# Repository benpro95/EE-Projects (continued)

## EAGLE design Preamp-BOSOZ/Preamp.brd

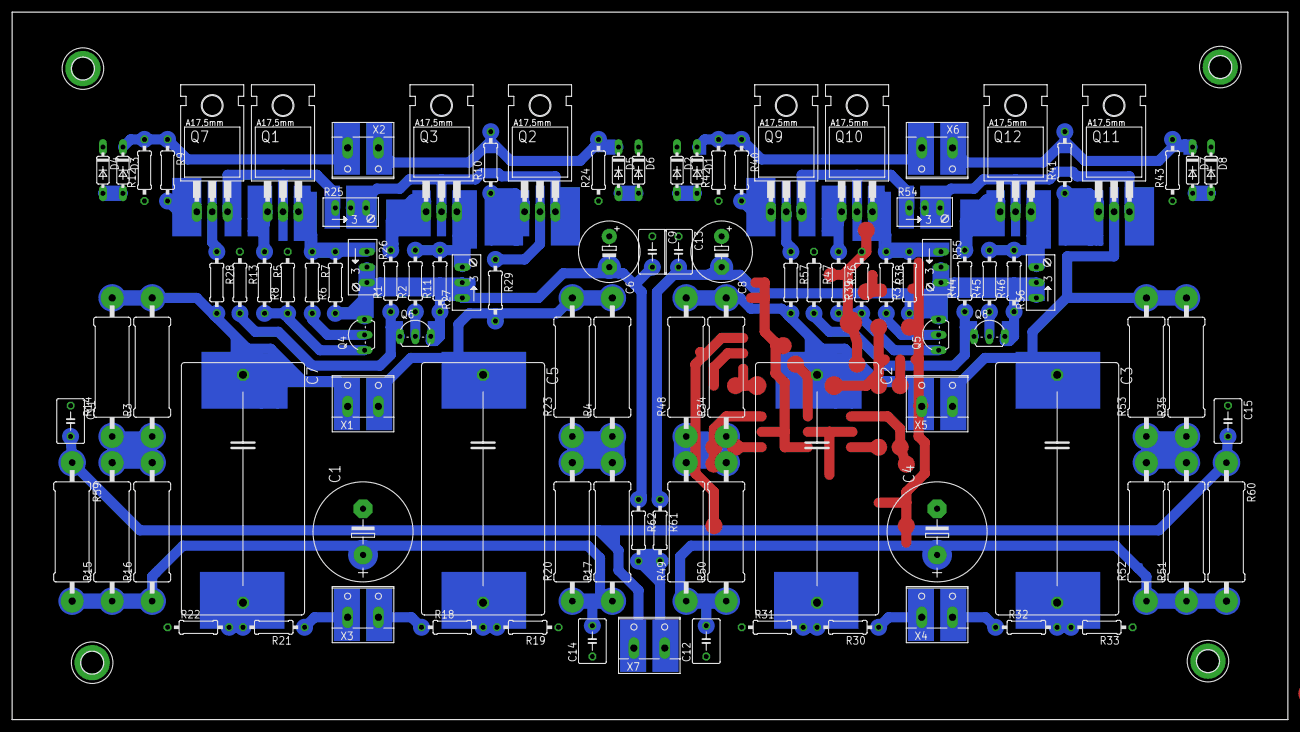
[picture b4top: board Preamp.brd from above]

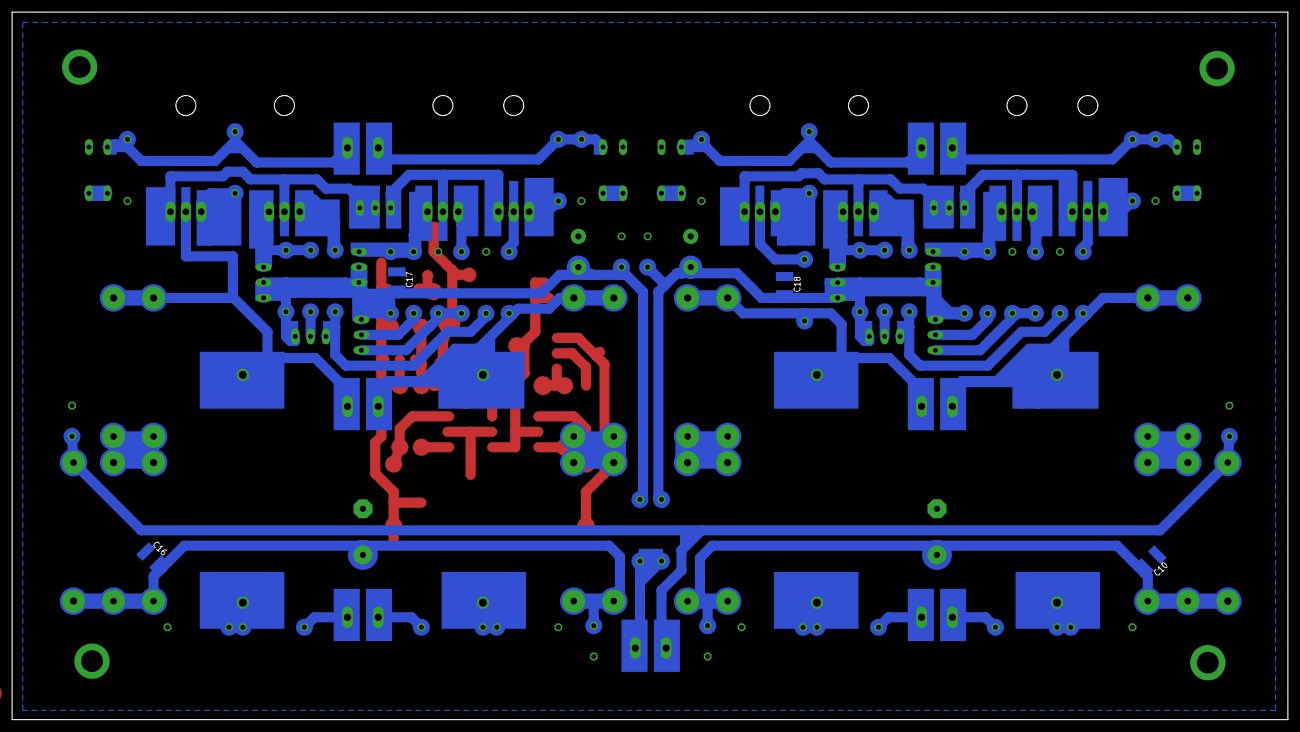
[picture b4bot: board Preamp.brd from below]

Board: 2 copper layers, 210.5 x 116.8 mm, 110 parts (4 on the bottom side), 58 nets.

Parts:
C1, C4: 220uF; E7,5-16
C2, C3, C5, C7: 11uF; C375-203X418
C6, C8: 100uF; E5-10,5
C9, C11, C12, C13, C14, C15: .6; C050-045X075
C10, C16, C17, C18: 3n9; C1210K
D1, D2, D3, D4, D5, D6, D7, D8: 9V1; DO35-7
H1, H2, H3, H4: MOUNT-PAD-ROUND3.6; 3,6-PAD
Q1, Q2, Q3, Q7, Q9, Q10, Q11, Q12: NFET; TO220BH
Q4, Q5, Q6, Q8: BC546A; TO92-EBC
R1, R2, R5, R7, R9, R10, R18, R21, R30, R32, R36, R38, R40, R41, R44, R45: 200; 0207/10
R3, R4, R14, R15, R16, R17, R20, R23, R34, R35, R48, R49, R50, R51, R52, R53: 1K; 0617/22
R6, R11, R37, R46: 27; 0207/10
R8, R13, R39, R47: 1K8; 0207/10
R12, R24, R42, R43: 24K5; 0207/10
R19, R22, R31, R33: 200K; 0207/10
R25, R54: 1K; RJ9W
R26, R27, R55, R56: 500; RJ9W
R28, R29, R57: 0; 0207/10
R59, R60: 47; 0617/22
R61, R62: 5R1; 0207/10
X1, X2, X3, X4, X5, X6, X7: W237-132

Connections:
GND: C1.-, C4.-, C6.+, C8.+, C9.1, C10.1, C11.1, C12.1, C13.1, C14.1, C15.1, C16.1, C17.1, C18.1, D2.C, D4.C, D6.C, D8.C, R8.2, R12.1, R13.1, R19.1, R22.1, R24.1, R31.1, R33.1, R39.2, R42.1, R43.1, R47.1
unnamed: Q3.S, R2.2, R11.2, R27.A
unnamed: Q3.G, R1.2
unnamed: Q6.B, R2.1
unnamed: Q6.C, R1.1, R13.2
unnamed: Q1.G, R5.1
unnamed: C6.-, C9.2, C18.2, Q4.E, Q6.E, R6.1, R11.1, R26.A, R26.S, R27.E, R27.S, R62.1
unnamed: Q4.B, R7.2
unnamed: Q1.S, R6.2, R7.1, R26.E
unnamed: Q4.C, R5.2, R8.1
unnamed: Q7.G, R9.2
unnamed: R3.1, R14.1, R15.2, R16.2
unnamed: Q2.G, R10.1
unnamed: C7.1, R3.2, R14.2, R28.2, X1.1
unnamed: Q1.D, Q7.S, R25.E
unnamed: D3.C, R9.1, R12.2, X2.2
unnamed: Q2.S, Q3.D, R25.A, R25.S
unnamed: D5.C, R10.2, R24.2, X2.1
unnamed: Q7.D, R28.1
unnamed: R4.1, R17.2, R20.2, R23.1
unnamed: Q2.D, R29.1
unnamed: R21.1, X3.1
unnamed: C1.+, C10.2, C14.2, R15.1, R16.1, R17.1, R20.1, R59.2
unnamed: C2.1, R34.2, R48.2, R57.2, X5.1
unnamed: C2.2, R30.2, R31.2
unnamed: C3.2, R32.2, R33.2
unnamed: C7.2, R21.2, R22.2
unnamed: C5.2, R18.2, R19.2
unnamed: R30.1, X4.1
unnamed: C5.1, R4.2, R23.2, R29.2, X1.2
unnamed: R32.1, X4.2
unnamed: Q10.G, R36.1
unnamed: C8.-, C13.2, C17.2, Q5.E, Q8.E, R37.1, R46.1, R55.A, R55.S, R56.E, R56.S, R61.1
unnamed: Q5.B, R38.2
unnamed: Q10.S, R37.2, R38.1, R55.E
unnamed: Q5.C, R36.2, R39.1
unnamed: R18.1, X3.2
unnamed: D1.C, R40.1, R42.2, X6.2
unnamed: D7.C, R41.2, R43.2, X6.1
unnamed: D1.A, D2.A
unnamed: D7.A, D8.A
unnamed: Q12.S, R45.2, R46.2, R56.A
unnamed: Q12.G, R44.2
unnamed: Q8.B, R45.1
unnamed: Q8.C, R44.1, R47.2
unnamed: Q9.S, Q10.D, R54.E
unnamed: Q11.S, Q12.D, R54.A, R54.S
unnamed: R34.1, R48.1, R49.2, R50.2
unnamed: R35.1, R51.2, R52.2, R53.1
unnamed: C4.+, C12.2, C16.2, R49.1, R50.1, R51.1, R52.1, R60.2
unnamed: Q9.G, R40.2
unnamed: Q11.G, R41.1
unnamed: Q9.D, R57.1
unnamed: C3.1, Q11.D, R35.2, R53.2, X5.2
unnamed: C11.2, C15.2, R59.1, R60.1, X7.1
unnamed: R61.2, R62.2, X7.2
unnamed: D3.A, D4.A
unnamed: D5.A, D6.A

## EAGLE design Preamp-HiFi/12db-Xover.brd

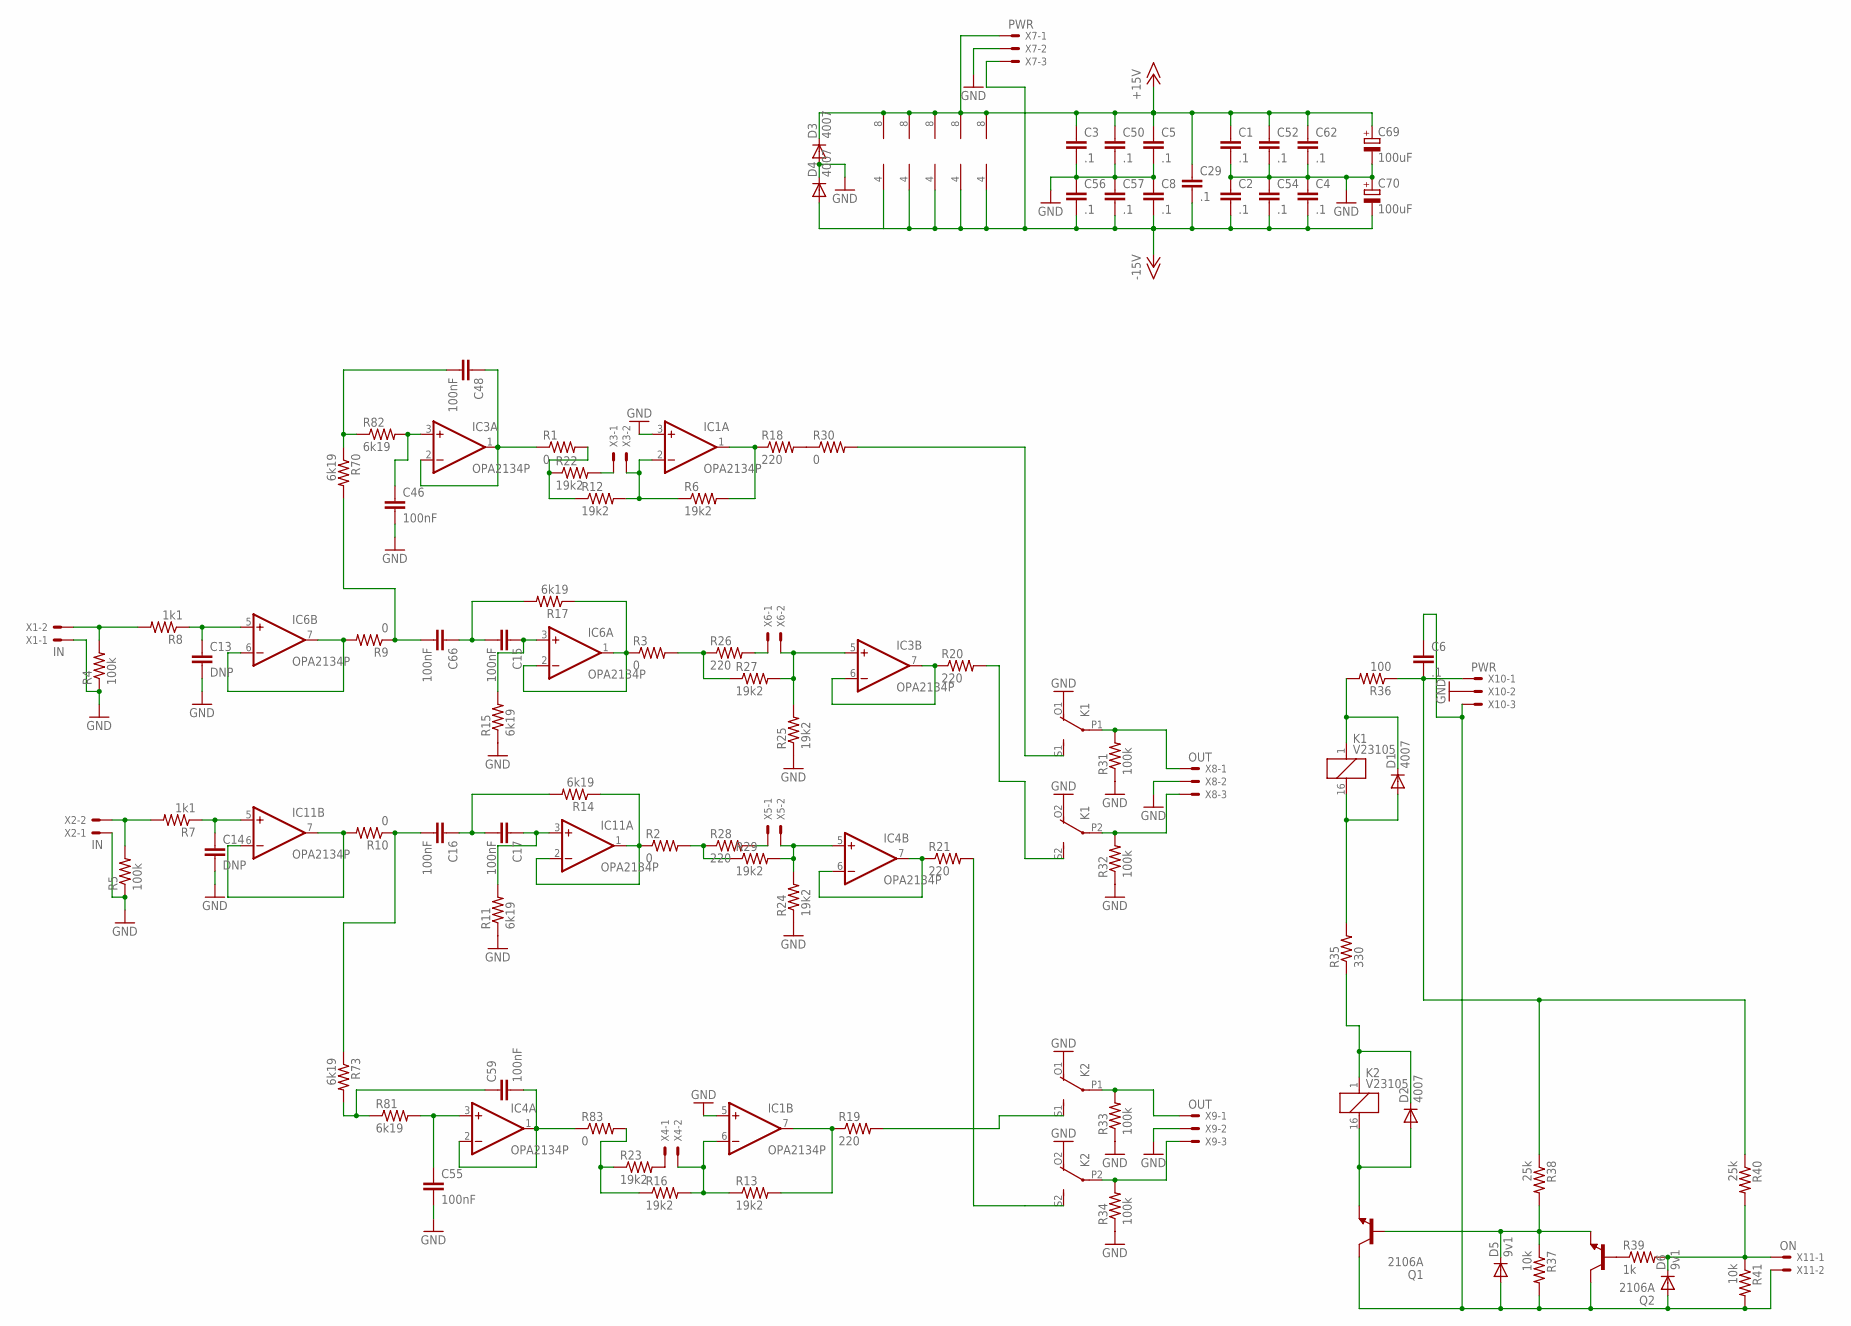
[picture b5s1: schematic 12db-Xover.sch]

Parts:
C1, C2, C3, C4, C5, C6, C8, C29, C50, C52, C54, C56, C57, C62: .1; C4532
C13, C14: DNP; C050-035X075
C15, C16, C17, C46, C48, C55, C59, C66: 100nF; C050-075X075
C69, C70: 100uF; E3,5-10
D1, D2, D3, D4: 4007; DO35-10
D5, D6: 9v1; DO35-7
IC1, IC3, IC4, IC6, IC11: OPA2134P; DIL08
K1, K2: V23105; 351
Q1, Q2: 2106A; TO92-EBC
R1, R3: 0; 0309/12
R2, R9, R10, R30, R83: 0; 0309/10
R4, R5, R31, R32, R33, R34: 100k; 0309/10
R6, R12, R13, R16, R22, R23, R27, R29: 19k2; 0309/10
R7, R8: 1k1; 0309/10
R11, R15, R70, R73, R81, R82: 6k19; 0309/12
R14, R17: 6k19; 0309/10
R18, R20: 220; 0309/12
R19, R21, R26, R28: 220; 0309/10
R24, R25: 19k2; 0309/12
R35: 330; 0411/15
R36: 100; 0309/12
R37, R41: 10k; 0309/12
R38, R40: 25k; 0309/10
R39: 1k; 0309/10
X1, X2: IN; 22-23-2021
X3, X4, X5, X6: 22-23-2021
X7, X10: PWR; 22-23-2031
X8, X9: OUT; 22-23-2031
X11: ON; 22-23-2021

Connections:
+15V: C1.1, C3.1, C5.1, C29.1, C50.1, C52.1, C62.1, C69.+, D3.C, IC1.8 (V+), IC3.8 (V+), IC4.8 (V+), IC6.8 (V+), IC11.8 (V+), X7.1
-15V: C2.2, C4.2, C8.2, C29.2, C54.2, C56.2, C57.2, C70.-, D4.A, IC1.4 (V-), IC3.4 (V-), IC4.4 (V-), IC6.4 (V-), IC11.4 (V-), X7.3
GND: C1.2, C2.1, C3.2, C4.1, C5.2, C8.1, C13.2, C14.2, C46.2, C50.2, C52.2, C54.1, C55.2, C56.1, C57.1, C62.2, C69.-, C70.+, D3.A, D4.C, IC1.3 (+IN), IC1.5 (+IN), K1.O1 (O), K1.O2 (O), K2.O1 (O), K2.O2 (O), R4.1, R5.1, R11.1, R15.1, R24.1, R25.1, R31.1, R32.1, R33.1, R34.1, X1.1, X2.1, X7.2, X8.2, X9.2, X10.2
unnamed: IC6.1 (OUT), IC6.2 (-IN), R3.1, R17.1
unnamed: IC3.5 (+IN), R25.2, R27.2, X6.2
unnamed: IC11.6 (-IN), IC11.7 (OUT), R10.2
unnamed: IC4.5 (+IN), R24.2, R29.2, X5.2
unnamed: C14.1, IC11.5 (+IN), R7.1
unnamed: R5.2, R7.2, X2.2
unnamed: R4.2, R8.2, X1.2
unnamed: C13.1, IC6.5 (+IN), R8.1
unnamed: IC6.6 (-IN), IC6.7 (OUT), R9.2
unnamed: IC1.2 (-IN), R6.1, R12.2, X3.2
unnamed: IC1.6 (-IN), R13.1, R16.2, X4.2
unnamed: C15.1, IC6.3 (+IN), R15.2
unnamed: C15.2, C66.1, R17.2
unnamed: IC1.1 (OUT), R6.2, R18.1
unnamed: C16.1, C17.2, R14.2
unnamed: C17.1, IC11.3 (+IN), R11.2
unnamed: IC3.6 (-IN), IC3.7 (OUT), R20.1
unnamed: IC4.6 (-IN), IC4.7 (OUT), R21.1
unnamed: IC1.7 (OUT), R13.2, R19.1
unnamed: R22.2, X3.1
unnamed: R1.2, R12.1, R22.1
unnamed: R16.1, R23.1, R83.2
unnamed: R23.2, X4.1
unnamed: R26.2, X6.1
unnamed: R28.2, X5.1
unnamed: R3.2, R26.1, R27.1
unnamed: R2.2, R28.1, R29.1
unnamed: IC11.1 (OUT), IC11.2 (-IN), R2.1, R14.1
unnamed: R18.2, R30.1
unnamed: K2.P2, R34.2, X9.3
unnamed: K2.P1, R33.2, X9.1
unnamed: K1.P2, R32.2, X8.3
unnamed: K1.P1, R31.2, X8.1
unnamed: K1.S1 (S), R30.2
unnamed: K1.S2 (S), R20.2
unnamed: K2.S1 (S), R19.2
unnamed: K2.S2 (S), R21.2
unnamed: D2.C, K2.1, R35.1
unnamed: D1.A, K1.16 (2), R35.2
unnamed: D1.C, K1.1, R36.2
unnamed: D2.A, K2.16 (2), Q1.E
unnamed: C6.2, R36.1, R38.1, R40.1, X10.1
unnamed: C6.1, D5.A, D6.A, Q1.C, Q2.C, R37.2, R41.2, X10.3, X11.2
unnamed: D5.C, Q1.B, Q2.E, R37.1, R38.2
unnamed: Q2.B, R39.1
unnamed: D6.C, R39.2, R40.2, R41.1, X11.1
unnamed: C66.2, R9.1, R70.2
unnamed: C59.2, IC4.1 (OUT), IC4.2 (-IN), R83.1
unnamed: C48.1, IC3.1 (OUT), IC3.2 (-IN), R1.1
unnamed: C46.1, IC3.3 (+IN), R82.2
unnamed: C48.2, R70.1, R82.1
unnamed: C59.1, R73.2, R81.1
unnamed: C55.1, IC4.3 (+IN), R81.2
unnamed: C16.2, R10.1, R73.1

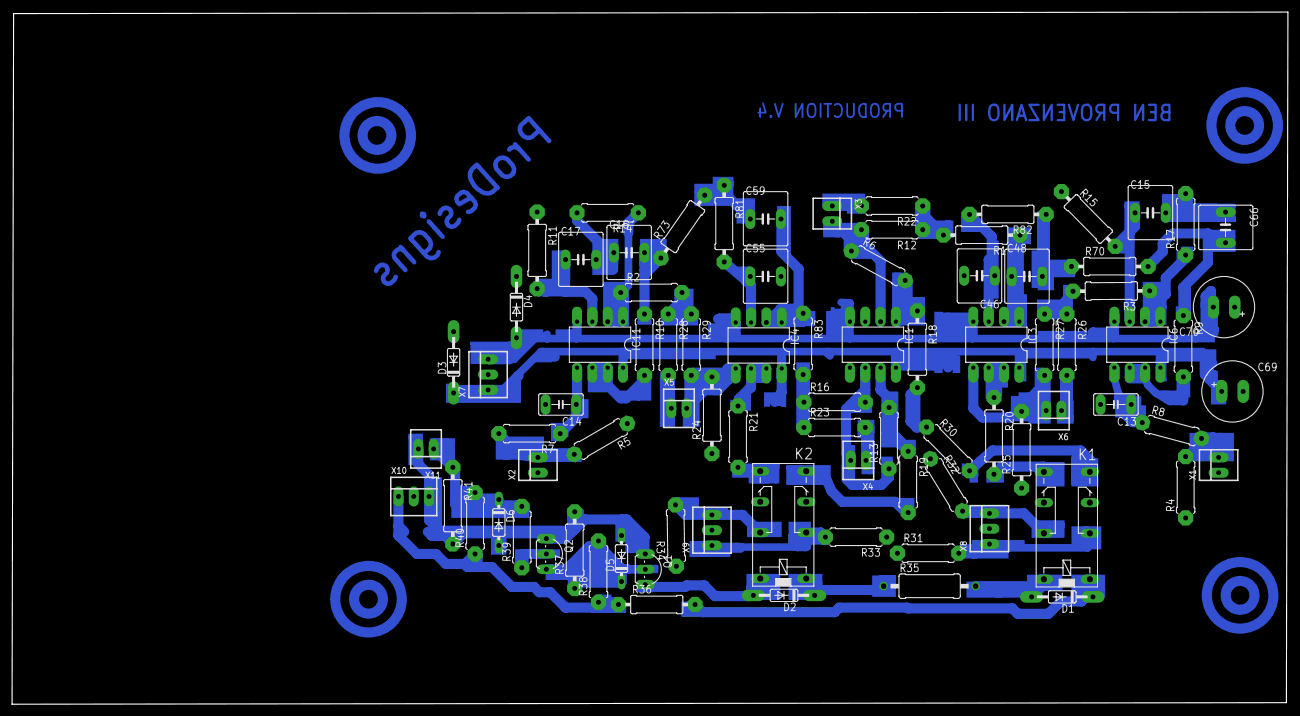
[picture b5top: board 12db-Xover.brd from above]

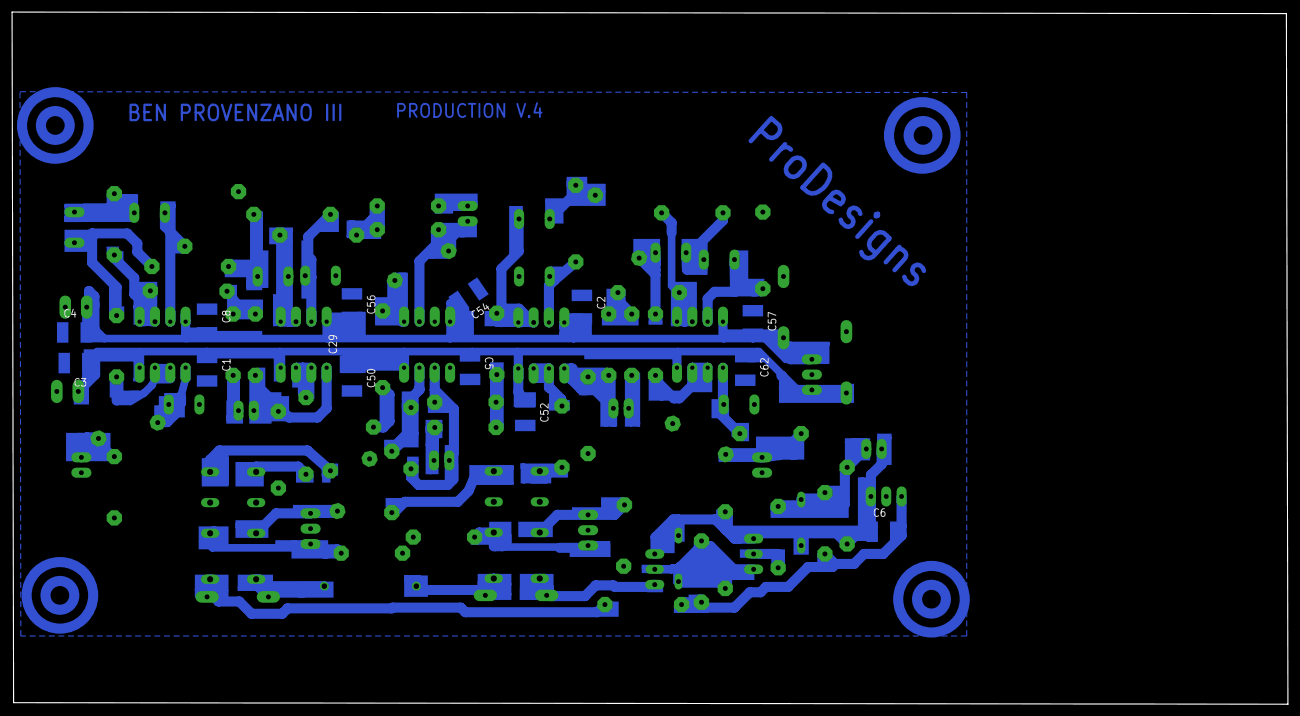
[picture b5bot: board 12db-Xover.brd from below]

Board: 2 copper layers, 211.4 x 114.7 mm, 98 parts (14 on the bottom side), 57 nets.

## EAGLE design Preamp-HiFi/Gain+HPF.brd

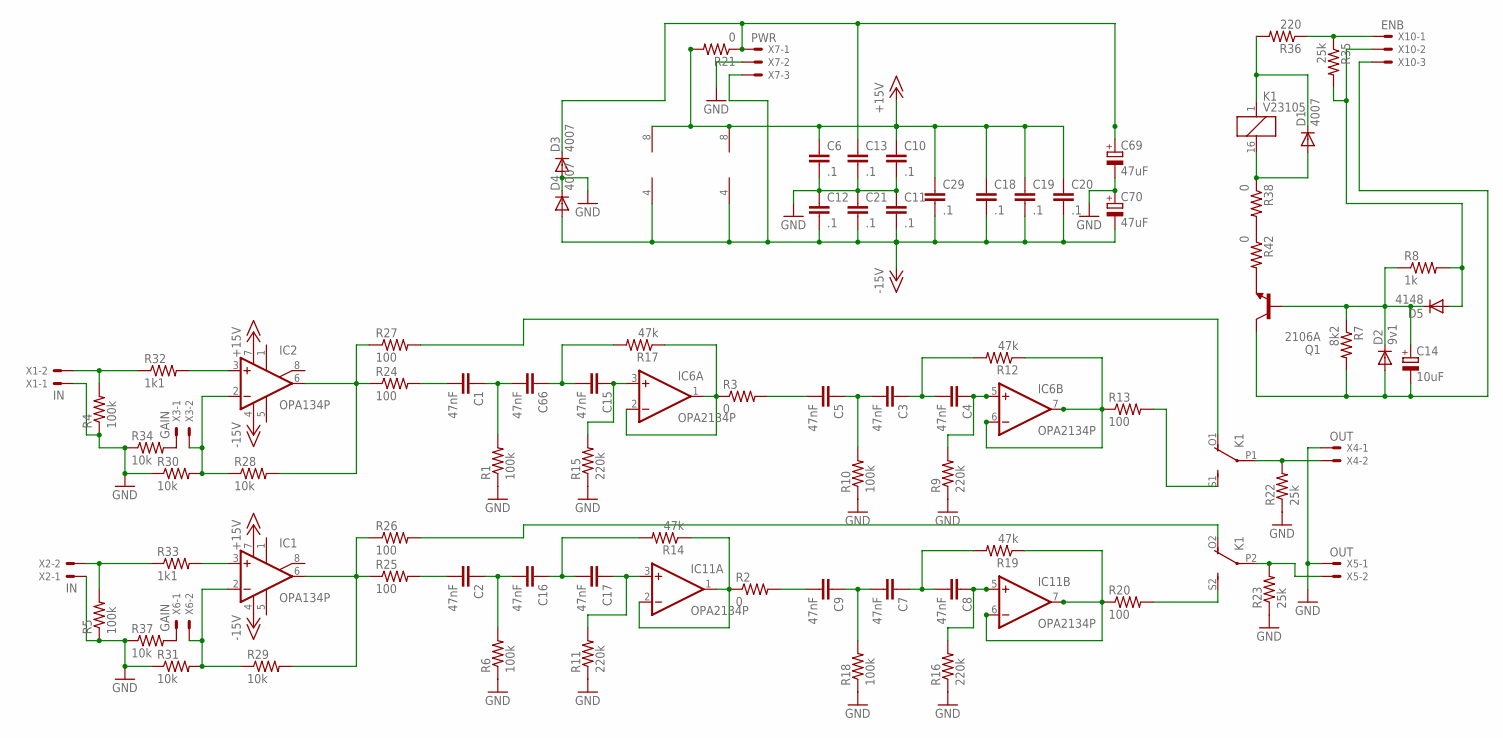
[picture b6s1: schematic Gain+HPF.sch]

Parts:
C1, C2, C3, C4, C5, C7, C8, C9, C15, C16, C17, C66: 47nF; C050-075X075
C6, C10, C11, C12, C13, C18, C19, C20, C21, C29: .1; C4532
C14: 10uF; E2,5-6
C69, C70: 47uF; E2,5-7
D1: 4007; DO35-7
D2: 9v1; DO35-7
D3, D4: 4007; DO35-10
D5: 4148; DO35-7
IC1, IC2: OPA134P; DIL08
IC6, IC11: OPA2134P; DIL08
K1: V23105; 351
Q1: 2106A; TO92-EBC
R1, R6, R10, R18: 100k; 0309/10
R2, R21, R38, R42: 0; 0309/10
R3: 0; 0309/12
R4, R5: 100k; 0309/12
R7: 8k2; R1210
R8: 1k; R1210
R9, R11, R15, R16: 220k; 0309/10
R12, R14, R17, R19: 47k; 0309/10
R13, R20, R26, R27: 100; 0309/10
R22, R23, R35: 25k; 0309/10
R24, R25: 100; 0309/12
R28, R29, R30, R31, R34, R37: 10k; 0309/10
R32, R33: 1k1; 0309/10
R36: 220; 0309/10
X1, X2: IN; 22-23-2021
X3, X6: GAIN; 22-23-2021
X4, X5: OUT; 22-23-2021
X7: PWR; 22-23-2031
X10: ENB; 22-23-2031

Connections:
+15V: C6.1, C10.1, C18.1, C19.1, C20.1, C29.1, IC1.7 (V+), IC2.7 (V+), IC6.8 (V+), IC11.8 (V+), R21.2
-15V: C11.2, C12.2, C18.2, C19.2, C20.2, C21.2, C29.2, C70.-, D4.A, IC1.4 (V-), IC2.4 (V-), IC6.4 (V-), IC11.4 (V-), X7.3
GND: C6.2, C10.2, C11.1, C12.1, C13.2, C21.1, C69.-, C70.+, D3.A, D4.C, R1.1, R4.1, R5.1, R6.1, R9.1, R10.1, R11.1, R15.1, R16.1, R18.1, R22.1, R23.1, R30.1, R31.1, R34.1, R37.1, X1.1, X2.1, X4.1, X5.1, X7.2
unnamed: IC6.1 (OUT), IC6.2 (-IN), R3.1, R17.1
unnamed: IC6.6 (-IN), IC6.7 (OUT), R12.1, R13.1
unnamed: C4.1, IC6.5 (+IN), R9.2
unnamed: C3.1, C4.2, R12.2
unnamed: R5.2, R33.1, X2.2
unnamed: R4.2, R32.1, X1.2
unnamed: C14.-, D2.A, Q1.C, R7.2, X10.3
unnamed: C3.2, C5.1, R10.2
unnamed: C5.2, R3.2
unnamed: IC11.6 (-IN), IC11.7 (OUT), R19.1, R20.1
unnamed: C15.1, IC6.3 (+IN), R15.2
unnamed: C15.2, C66.1, R17.2
unnamed: C8.1, IC11.5 (+IN), R16.2
unnamed: C16.1, C17.2, R14.2
unnamed: C17.1, IC11.3 (+IN), R11.2
unnamed: C7.1, C8.2, R19.2
unnamed: C7.2, C9.1, R18.2
unnamed: IC2.6 (OUT), R24.1, R27.1, R28.2
unnamed: IC1.6 (OUT), R25.1, R26.1, R29.2
unnamed: K1.S1 (S), R13.2
unnamed: K1.S2 (S), R20.2
unnamed: C13.1, C69.+, D3.C, R21.1, X7.1
unnamed: K1.O1 (O), R27.2
unnamed: K1.O2 (O), R26.2
unnamed: C1.2, R24.2
unnamed: C9.2, R2.2
unnamed: IC11.1 (OUT), IC11.2 (-IN), R2.1, R14.1
unnamed: C2.2, R25.2
unnamed: IC2.3 (+IN), R32.2
unnamed: IC2.2 (-IN), R28.1, R30.2, X3.2
unnamed: K1.P2, R23.2, X5.2
unnamed: K1.P1, R22.2, X4.2
unnamed: IC1.3 (+IN), R33.2
unnamed: IC1.2 (-IN), R29.1, R31.2, X6.2
unnamed: R34.2, X3.1
unnamed: R37.2, X6.1
unnamed: C14.+, D2.C, D5.C, Q1.B, R7.1, R8.1
unnamed: D1.A, K1.16 (2), R38.1
unnamed: D1.C, K1.1, R36.2
unnamed: R35.1, R36.1, X10.1
unnamed: D5.A, R8.2, R35.2, X10.2
unnamed: Q1.E, R42.2
unnamed: R38.2, R42.1
unnamed: C1.1, C66.2, R1.2
unnamed: C2.1, C16.2, R6.2

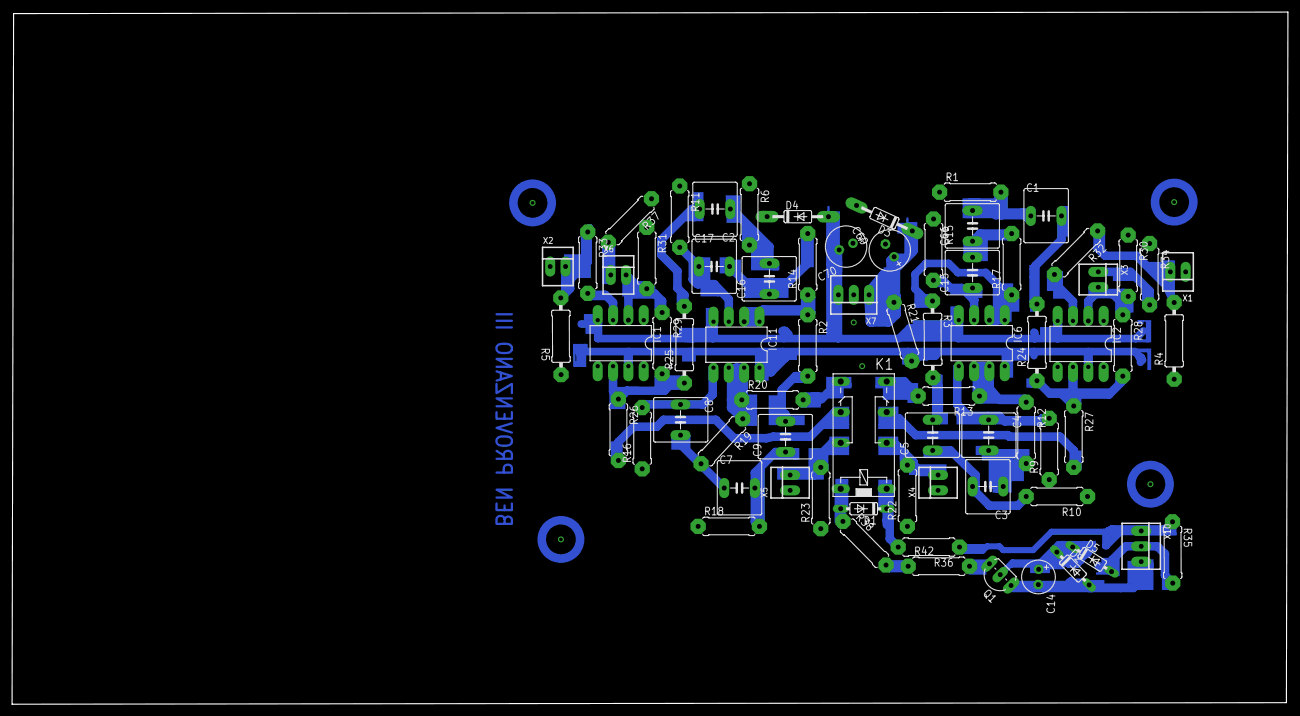
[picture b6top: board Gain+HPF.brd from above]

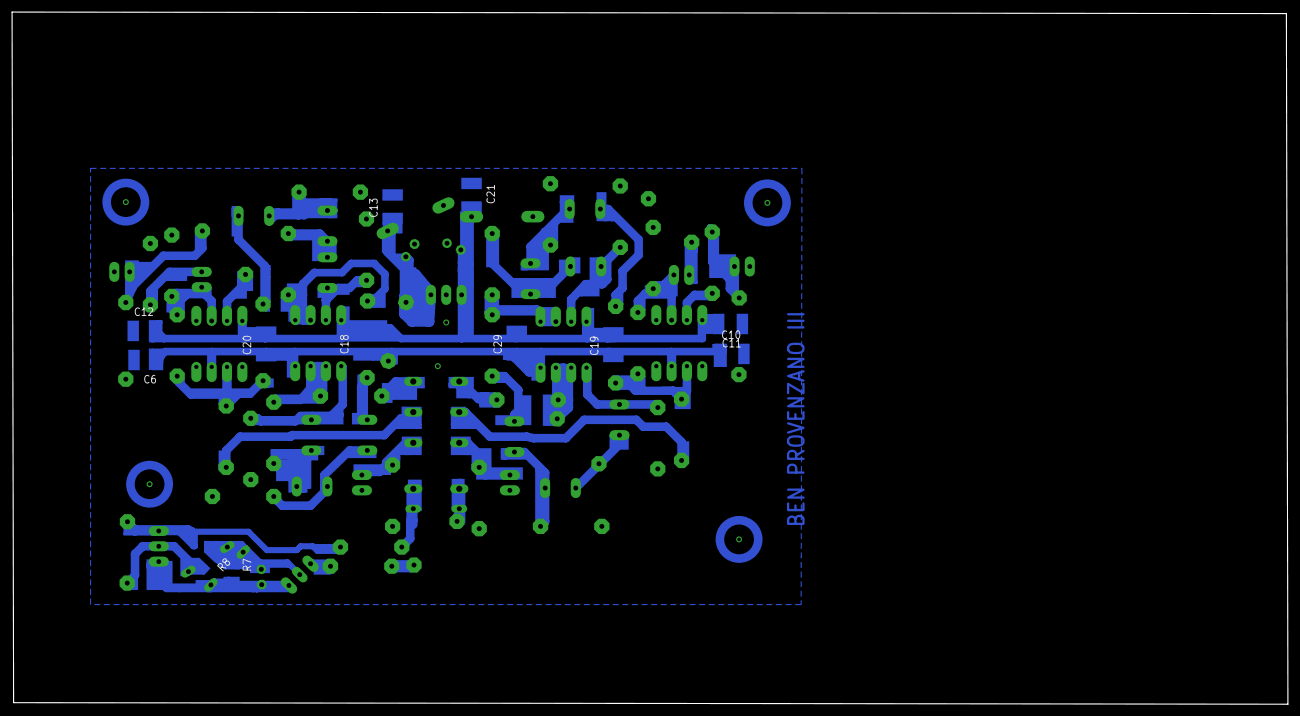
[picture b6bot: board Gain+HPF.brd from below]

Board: 2 copper layers, 211.4 x 114.7 mm, 83 parts (12 on the bottom side), 48 nets.

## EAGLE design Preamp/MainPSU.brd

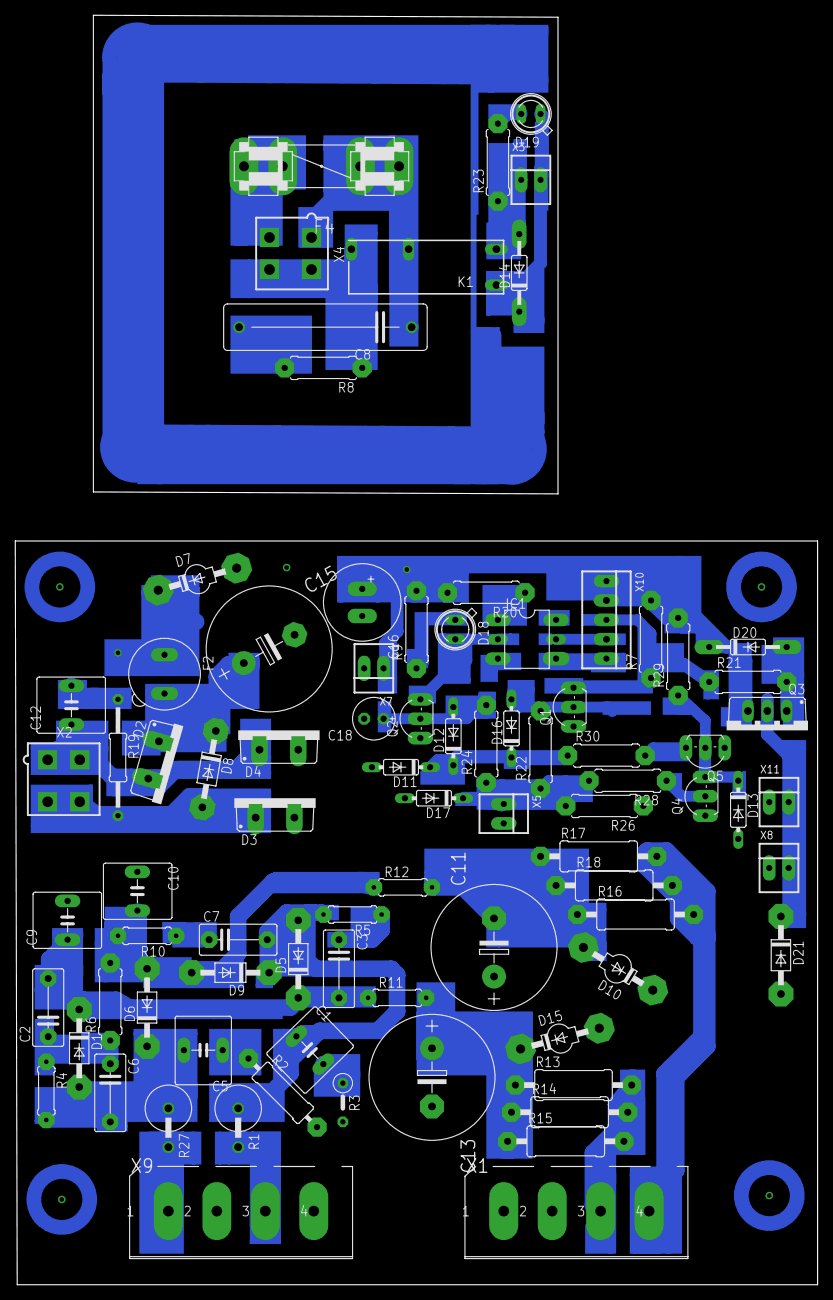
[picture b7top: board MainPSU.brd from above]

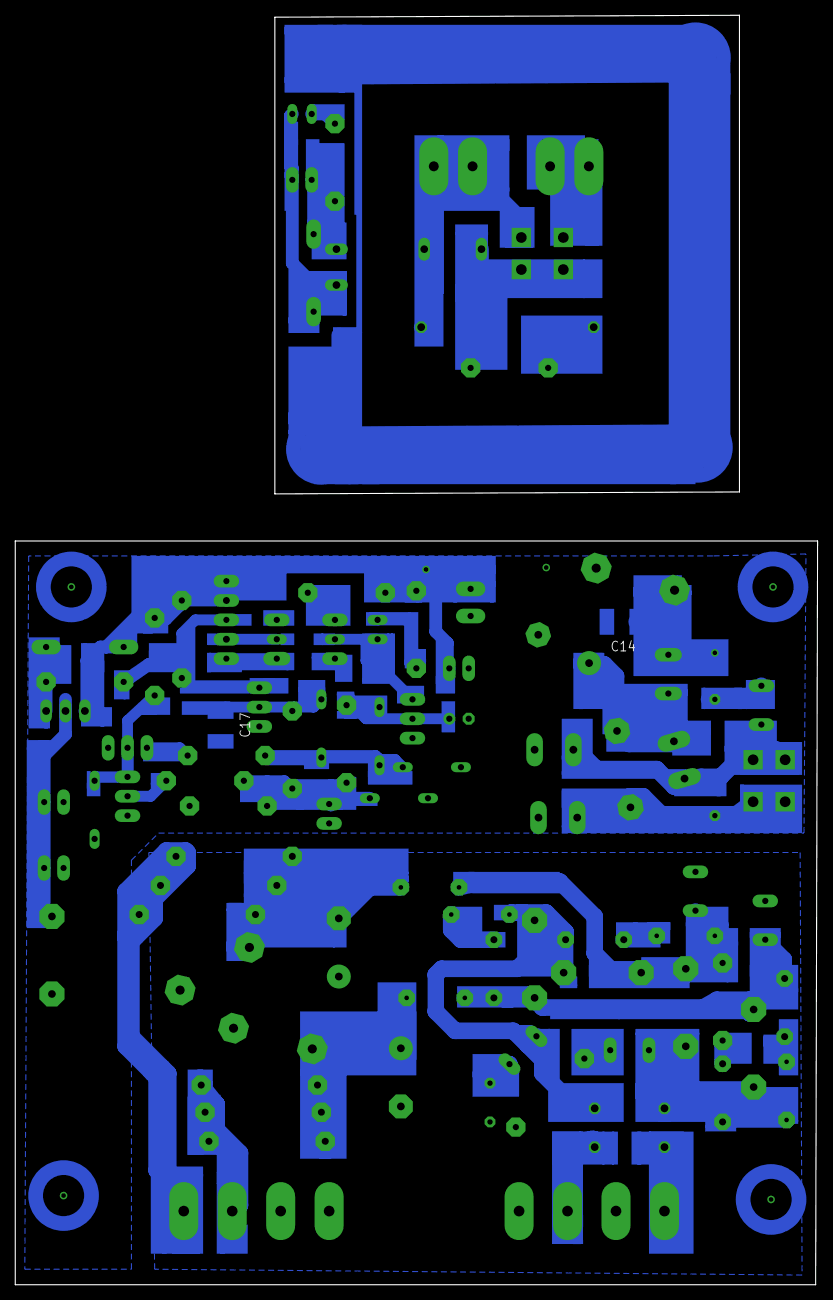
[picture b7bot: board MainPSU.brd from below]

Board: 2 copper layers, 105.1 x 97.5 mm, 86 parts (2 on the bottom side), 46 nets.

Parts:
C1, C5: 47nF; C050-075X075
C2, C3, C6, C7: 1nF; C075-042X103
C8: 47nF X2; C225-062X268
C9, C10: 33nF; C050-075X075
C11, C13: 1800uF; E7,5-16
C12: 100nF; C050-075X075
C14: .1; C1812
C15: 3300uF; E7,5-16
C16: 100uF; E3,5-10
C17: 1uF; C1812
C18: 10uF; E2,5-6E
D1, D5, D6, D9: MUR120; DO41-10
D2, D3, D4: 3A; DO220S
D7: TVS20V; SOD57-10
D8: 3A; DO41-10
D10, D15: TVS36V; SOD57-10
D11, D13, D17: 9v1; DO35-7
D12, D16: 4148; DO35-7
D14: 4007; DO35-10
D18, D19: LED; SFH482
D20: 9v1; DO35-10
D21: 4007; DO41-10
F2: 1A; 19560
F4: 250mA; FUSE1
IC1: 4N28; DIL06
K1: G5NB; LD
Q1, Q2, Q4, Q5: ZVN2106; TO92-EBC
Q3: PMOS; TO220BV
R1, R27: 2.2; 0617V
R2: 100; 0309/12
R3: 100; 0207/5V
R4, R5, R10: 1k; 0207/7
R6, R28: 1k; 0309/10
R7, R23: 2k2; 0309/10
R8: 5.1; 0309/10
R9: 1k74; 0309/10
R11, R12: .5A PTC; 0207/7
R13, R14, R15, R16, R17, R18: 68; 0411/15
R19: 220; 0207/15
R20: 330; 0309/10
R21, R26, R29: 4k7; 0309/10
R22, R24: 1M; 0309/10
R30: 220; 0309/10
X1: DC; GMSTBA4
X2: 9VAC; 5566-4
X3: RELAY; 22-23-2021
X4: LINE; 5566-4
X5: PG; 22-23-2021
X7: 5V; 22-23-2021
X8, X11: 5V-AUX; 22-23-2021
X9: AC; GMSTBA4
X10: 22-23-2051

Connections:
DGND: C9.2, C10.1, C11.+, C13.-, D10.C, D15.A, R2.2, R3.2, X1.1, X1.2, X9.2, X9.4
GND: C14.2, C15.-, C16.-, C17.2, C18.-, D3.A, D4.A, D7.A, D11.A, D13.A, D17.A, D21.A, Q1.C, Q2.C, Q4.C, Q5.C, R26.1, X5.2, X7.2, X8.1, X11.1
unnamed: R13.2, R14.2, R15.2, X1.3
unnamed: R16.2, R17.2, R18.2, X1.4
unnamed: R1.2, X9.3
unnamed: R27.2, X9.1
unnamed: C8.2, R8.2
unnamed: C5.1, R2.1
unnamed: C1.2, R3.1
unnamed: C13.+, D15.C, R11.2, R13.1, R14.1, R15.1
unnamed: C8.1, F4.1A, K1.COM, X4.1
unnamed: C12.2, R19.1
unnamed: D21.C, Q3.D, X8.2, X11.2
unnamed: C1.1, C7.2, D5.A, D9.C, R1.1, R5.2
unnamed: F4.2A, X4.3
unnamed: C2.1, R4.1
unnamed: C2.2, C3.2, C9.1, D1.C, D5.C, R11.1
unnamed: C5.2, C6.2, D1.A, D6.C, R4.2, R27.1
unnamed: K1.NO, R8.1, X4.2, X4.4
unnamed: C3.1, R5.1
unnamed: C11.-, D10.A, R12.2, R16.1, R17.1, R18.1
unnamed: C6.1, R6.1
unnamed: D3.C, D8.A, R19.2, X2.3, X2.4
unnamed: C10.2, D6.A, D9.A, R6.2, R10.2, R12.1
unnamed: C7.1, R10.1
unnamed: C16.+, D20.C, Q3.S, R7.2, R9.2, R20.2, R29.2, X7.1, X10.1, X10.2
unnamed: D18.K, IC1.2, Q2.E
unnamed: C12.1, D2.A, D4.C, X2.1, X2.2
unnamed: D14.A, K1.2, R23.1, X3.1
unnamed: D20.A, Q3.G, R21.2
unnamed: C18.+, D12.A, Q2.B, R24.2
unnamed: C17.1, D16.A, Q1.B, R22.2
unnamed: D17.C, R22.1, R24.1, R26.2, R28.2, X5.1
unnamed: Q4.B, R28.1
unnamed: D13.C, Q4.E, Q5.B, R29.1
unnamed: Q5.E, R30.2
unnamed: D11.C, D12.C, D16.C, R30.1
unnamed: D19.K, R23.2
unnamed: IC1.1, R20.1
unnamed: C15.+, D2.C, D8.C, F2.2
unnamed: C14.1, D7.C, F2.1
unnamed: D14.C, D19.A, K1.1, X3.2
unnamed: IC1.4, X10.5
unnamed: Q1.E, R7.1, R21.1, X10.3
unnamed: D18.A, R9.1
unnamed: IC1.5, X10.4
